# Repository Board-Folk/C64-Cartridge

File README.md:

# C64-Cartridge
A Basic C64 Cartridge

Requires:

1 x 74LS02

1 x 74LS273

1 x 27C128/256/512 EPROM

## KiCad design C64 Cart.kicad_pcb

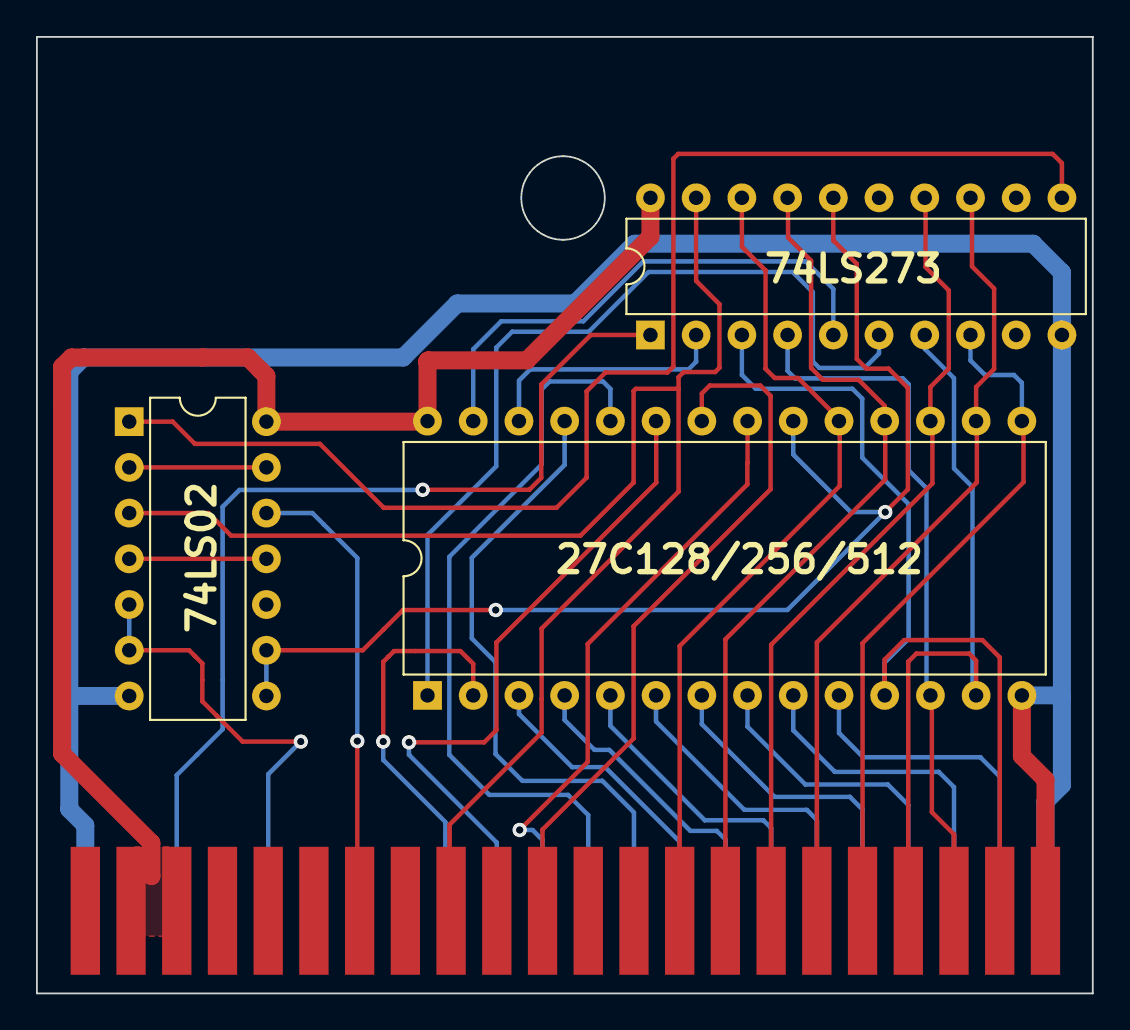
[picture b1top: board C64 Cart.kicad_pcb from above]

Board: 2 copper layers, 58.7 x 53.1 mm, 4 parts (0 on the bottom side), 35 nets.

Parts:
J1: Cart Edge; Edge Connector 2x22 2.54mm
U1: 74LS02; DIP-14_W7.62mm
U2: 74LS273; DIP-20_W7.62mm
U3: 27C512; DIP-28_W15.24mm

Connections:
/A0: J1.Y (Pin_24), U3.10 (A0)
/A1: J1.X (Pin_25), U3.9 (A1)
/A2: J1.W (Pin_26), U3.8 (A2)
/A3: J1.V (Pin_27), U3.7 (A3)
/A4: J1.U (Pin_28), U3.6 (A4)
/A5: J1.T (Pin_29), U3.5 (A5)
/A6: J1.S (Pin_30), U3.4 (A6)
/A7: J1.R (Pin_31), U3.3 (A7)
/A8: J1.P (Pin_32), U3.25 (A8)
/A9: J1.N (Pin_33), U3.24 (A9)
/A10: J1.M (Pin_34), U3.21 (A10)
/A11: J1.L (Pin_35), U3.23 (A11)
/A12: J1.K (Pin_36), U3.2 (A12)
/Cp: U1.1, U2.11 (Cp)
/D0: J1.21, U2.3 (D0), U3.11 (D0)
/D1: J1.20, U2.4 (D1), U3.12 (D1)
/D2: J1.19, U2.7 (D2), U3.13 (D2)
/D3: J1.18, U2.8 (D3), U3.15 (D3)
/D4: J1.17, U2.13 (D4), U3.16 (D4)
/D5: J1.16, U2.14 (D5), U3.17 (D5)
/D6: J1.15, U2.17 (D6), U3.18 (D6)
/D7: J1.14, U2.18 (D7), U3.19 (D7)
/PHI2: J1.E (Pin_40), U1.5, U1.6
/Q0: U2.2 (Q0), U3.26 (A13)
/Q1: U2.5 (Q1), U3.27 (A14)
/Q2: U2.6 (Q2), U3.1 (A15)
/Q7: J1.9, U1.3, U2.19 (Q7)
/_IO1: J1.7, U1.12
/_RESET: J1.C (Pin_42), U2.1 (~Mr)
/_ROML: J1.11, U3.22 (~OE)
/~CE: U1.8, U1.9, U2.16 (Q6), U3.20 (~CE)
GND: J1.22, J1.A (Pin_44), J1.Z (Pin_23), U1.7 (GND), U2.10 (GND), U3.14 (GND)
unnamed: U1.4, U1.11
unnamed: U1.2, U1.13
VCC: J1.2, J1.3, U1.14 (VCC), U2.20 (VCC), U3.28 (VCC)

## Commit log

2023-11-08 Ignore LCKs
2023-11-08 Initial Push
